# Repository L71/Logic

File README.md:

Logic signal processing Eurorack modules
========================================

* 4520 - 8bit binary counter/clock divider. Can trigger on both clock signal edges (determined by which input is used). 

* 234 - Sync clock divider, one pulse out for every 2,3 or 4 in. 

* Trigger - small module with 2x gate rising edge detectors, 2x inverters with button. Additional ORed output for the two edge detector outputs.

Panels and PCBs licensed cc-by-sa.

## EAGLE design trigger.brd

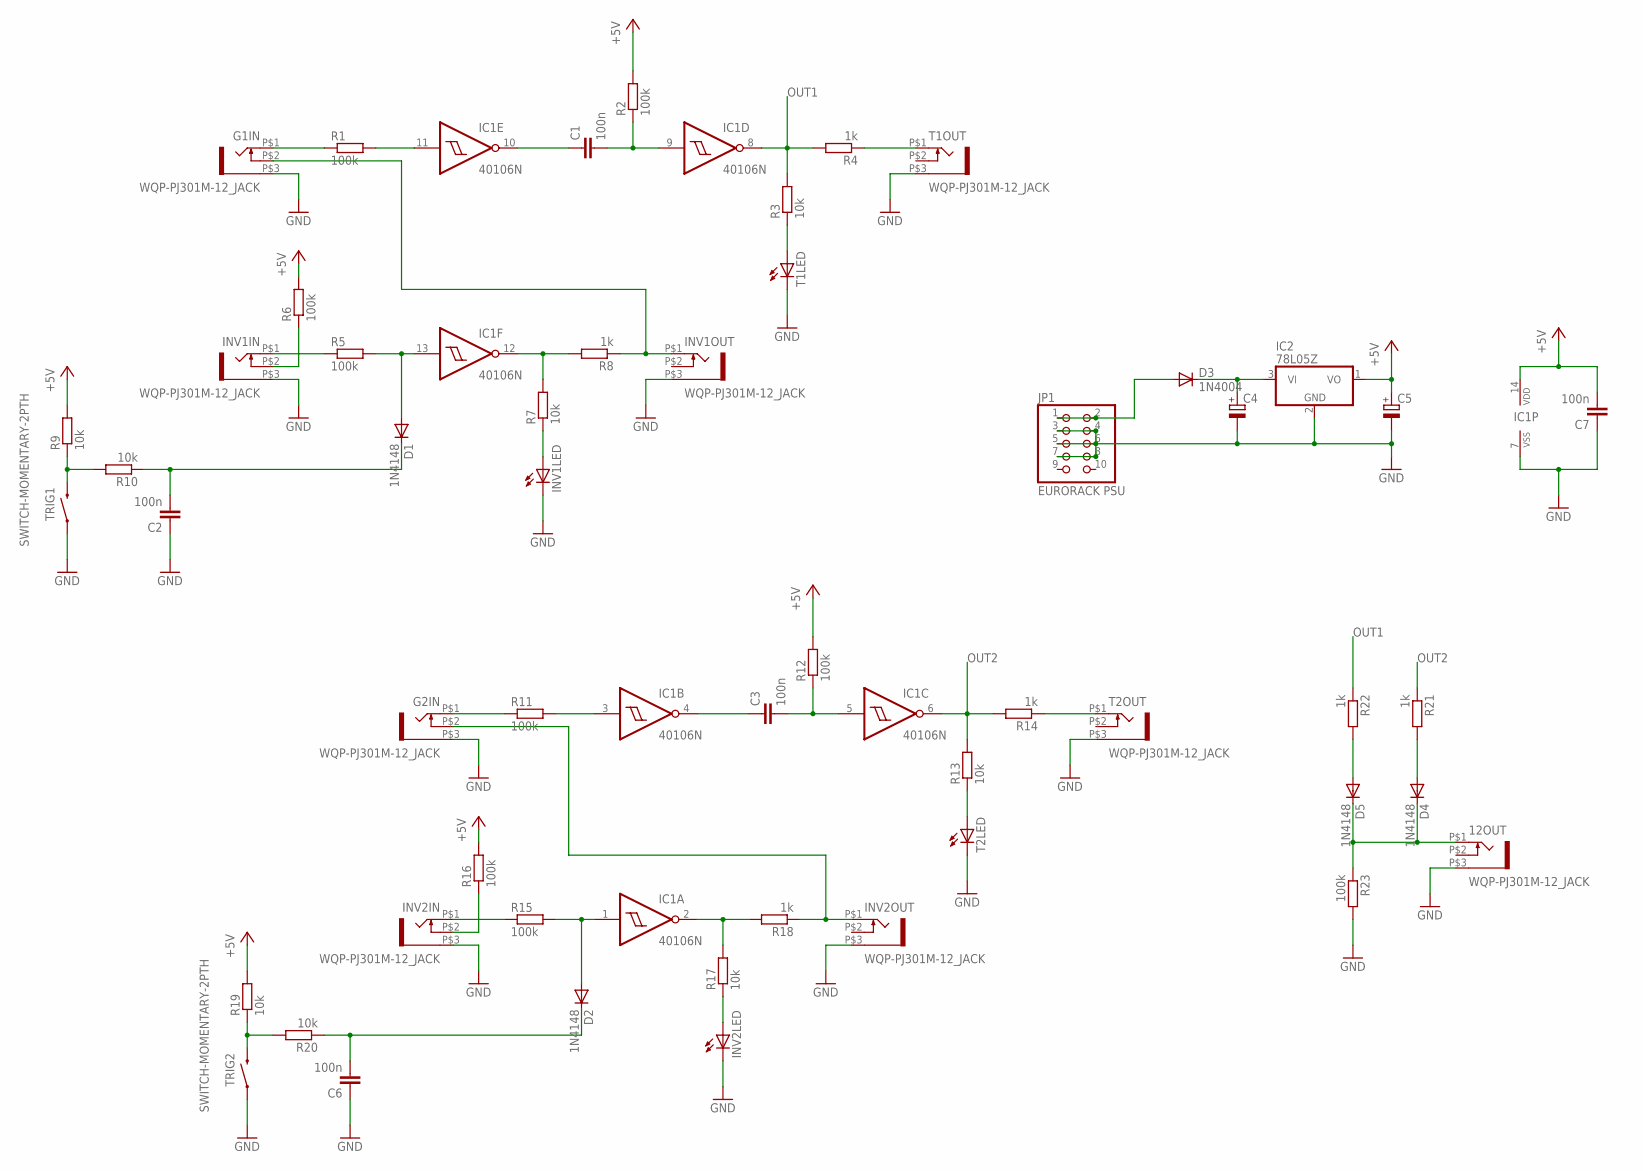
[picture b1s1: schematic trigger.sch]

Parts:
12OUT: WQP-PJ301M-12_JACK
C1, C2, C3, C6, C7: 100n; C025-025X050
C4, C5: CPOL-EUE2.5-5; E2,5-5
D1, D2, D4, D5: 1N4148; D-2.5
D3: 1N4004; D-2.5
G1IN, G2IN: WQP-PJ301M-12_JACK
IC1: 40106N; DIL14
IC2: 78L05Z; TO92
INV1IN, INV1OUT, INV2IN, INV2OUT: WQP-PJ301M-12_JACK
INV1LED, INV2LED: LED3MM
JP1: EURORACK PSU; 2X05
R1, R2, R5, R6, R11, R12, R15, R16, R23: 100k; 0204V
R3, R7, R9, R10, R13, R17, R19, R20: 10k; 0204V
R4, R8, R14, R18, R21, R22: 1k; 0204V
T1LED, T2LED: LED3MM
T1OUT, T2OUT: WQP-PJ301M-12_JACK
TRIG1, TRIG2: SWITCH-MOMENTARY-2PTH; TACTILE-PTH

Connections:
+5V: C5.+, C7.2, IC1.14 (VDD), IC2.1 (VO), R2.2, R6.2, R9.2, R12.2, R16.2, R19.2
+12V_IN: D3.A, JP1.1, JP1.2
GND: 12OUT.P$3 (1), C2.1, C4.-, C5.-, C6.1, C7.1, G1IN.P$3 (1), G2IN.P$3 (1), IC1.7 (VSS), IC2.2 (GND), INV1IN.P$3 (1), INV1LED.K (C), INV1OUT.P$3 (1), INV2IN.P$3 (1), INV2LED.K (C), INV2OUT.P$3 (1), JP1.3, JP1.4, JP1.5, JP1.6, JP1.7, JP1.8, R23.2, T1LED.K (C), T1OUT.P$3 (1), T2LED.K (C), T2OUT.P$3 (1), TRIG1.1, TRIG2.1
IN_1: G1IN.P$1 (2), R1.1
unnamed: 12OUT.P$1 (2), D4.C, D5.C, R23.1
unnamed: IC1.11 (I), R1.2
unnamed: C1.1, IC1.10 (O)
unnamed: C1.2, IC1.9 (I), R2.1
unnamed: D5.A, R22.2
unnamed: R3.1, T1LED.A
unnamed: R4.1, T1OUT.P$1 (2)
unnamed: IC1.12 (O), R7.2, R8.2
unnamed: INV1LED.A, R7.1
unnamed: G1IN.P$2 (3), INV1OUT.P$1 (2), R8.1
unnamed: INV1IN.P$1 (2), R5.1
unnamed: D1.A, IC1.13 (I), R5.2
unnamed: INV1IN.P$2 (3), R6.1
unnamed: C4.+, D3.C, IC2.3 (VI)
unnamed: R9.1, R10.2, TRIG1.3 (2)
unnamed: C2.2, D1.C, R10.1
unnamed: G2IN.P$1 (2), R11.1
unnamed: IC1.3 (I), R11.2
unnamed: C3.1, IC1.4 (O)
unnamed: C3.2, IC1.5 (I), R12.1
unnamed: D4.A, R21.2
unnamed: R13.1, T2LED.A
unnamed: R14.1, T2OUT.P$1 (2)
unnamed: IC1.2 (O), R17.2, R18.2
unnamed: INV2LED.A, R17.1
unnamed: G2IN.P$2 (3), INV2OUT.P$1 (2), R18.1
unnamed: INV2IN.P$1 (2), R15.1
unnamed: D2.A, IC1.1 (I), R15.2
unnamed: INV2IN.P$2 (3), R16.1
unnamed: R19.1, R20.2, TRIG2.3 (2)
unnamed: C6.2, D2.C, R20.1
OUT1: IC1.8 (O), R3.2, R4.2, R22.1
OUT2: IC1.6 (O), R13.2, R14.2, R21.1

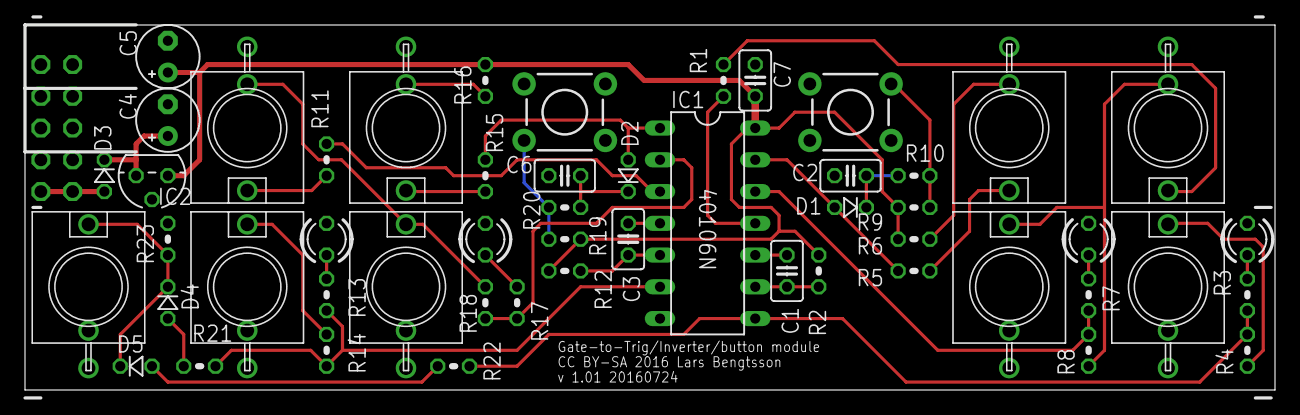
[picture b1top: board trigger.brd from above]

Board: 2 copper layers, 100.0 x 29.2 mm, 53 parts (1 on the bottom side), 37 nets.

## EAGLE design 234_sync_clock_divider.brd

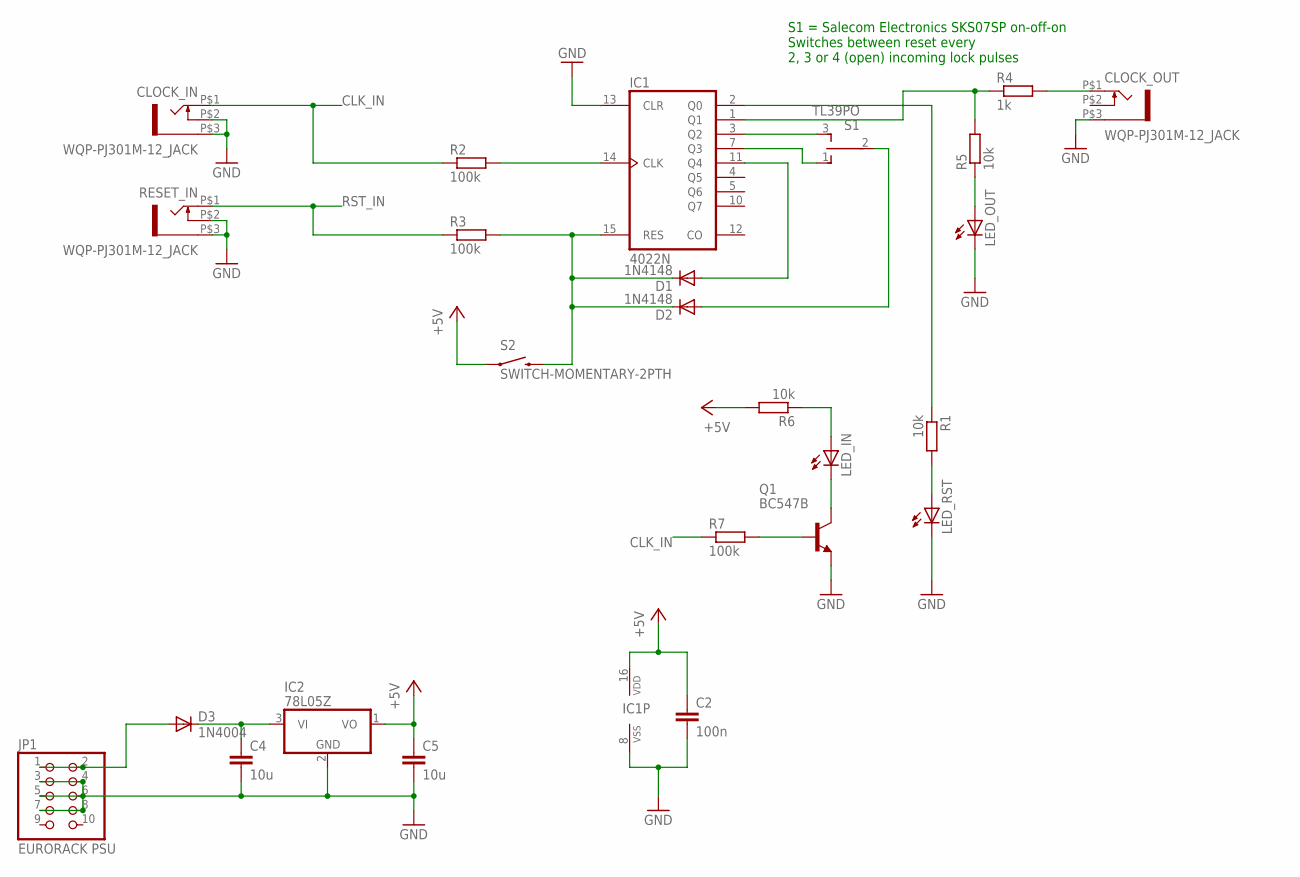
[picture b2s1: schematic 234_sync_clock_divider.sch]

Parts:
C2: 100n; C025-025X050
C4, C5: 10u; C1206K
CLOCK_IN: WQP-PJ301M-12_JACK
CLOCK_OUT: WQP-PJ301M-12_JACK
D1, D2: 1N4148; D-2.5
D3: 1N4004; D-2.5
IC1: 4022N; DIL16
IC2: 78L05Z; TO92
JP1: EURORACK PSU; 2X05
LED_IN: LED3MM
LED_OUT: LED3MM
LED_RST: LED3MM
Q1: BC547B; TO92
R1, R5, R6: 10k; 0204V
R2, R3, R7: 100k; 0204V
R4: 1k; 0204V
RESET_IN: WQP-PJ301M-12_JACK
S1: TL39PO; TL3XPO
S2: SWITCH-MOMENTARY-2PTH; TACTILE-PTH

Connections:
+5V: C2.1, C5.1, IC1.16 (VDD), IC2.1 (VO), R6.2, S2.1
+12V_IN: D3.A, JP1.1, JP1.2
CLK_IN: CLOCK_IN.P$1 (2), R2.1, R7.1
GND: C2.2, C4.2, C5.2, CLOCK_IN.P$2 (3), CLOCK_IN.P$3 (1), CLOCK_OUT.P$3 (1), IC1.8 (VSS), IC1.13 (CLR), IC2.2 (GND), JP1.3, JP1.4, JP1.5, JP1.6, JP1.7, JP1.8, LED_OUT.K (C), LED_RST.K (C), Q1.1 (E), RESET_IN.P$2 (3), RESET_IN.P$3 (1)
unnamed: LED_RST.A, R1.2
unnamed: IC1.14 (CLK), R2.2
unnamed: D1.C, D2.C, IC1.15 (RES), R3.2, S2.3 (2)
unnamed: IC1.2 (Q0), R1.1
unnamed: IC1.1 (Q1), R4.1, R5.2
unnamed: CLOCK_OUT.P$1 (2), R4.2
unnamed: LED_OUT.A, R5.1
unnamed: D1.A, IC1.11 (Q4)
unnamed: IC1.3 (Q2), S1.3 (S)
unnamed: IC1.7 (Q3), S1.1 (O)
unnamed: D2.A, S1.2
unnamed: C4.1, D3.C, IC2.3 (VI)
unnamed: LED_IN.A, R6.1
unnamed: LED_IN.K (C), Q1.3 (C)
unnamed: Q1.2 (B), R7.2
RST_IN: R3.1, RESET_IN.P$1 (2)

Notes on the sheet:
S1 = Salecom Electronics SKS07SP on-off-on Switches between reset every 2, 3 or 4 (open) incoming lock pulses

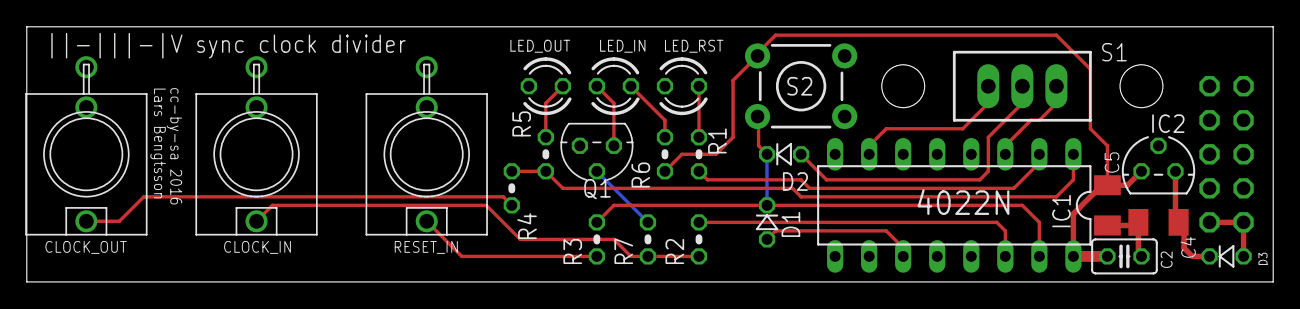
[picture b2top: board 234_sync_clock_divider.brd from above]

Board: 2 copper layers, 93.0 x 19.0 mm, 25 parts (1 on the bottom side), 20 nets.

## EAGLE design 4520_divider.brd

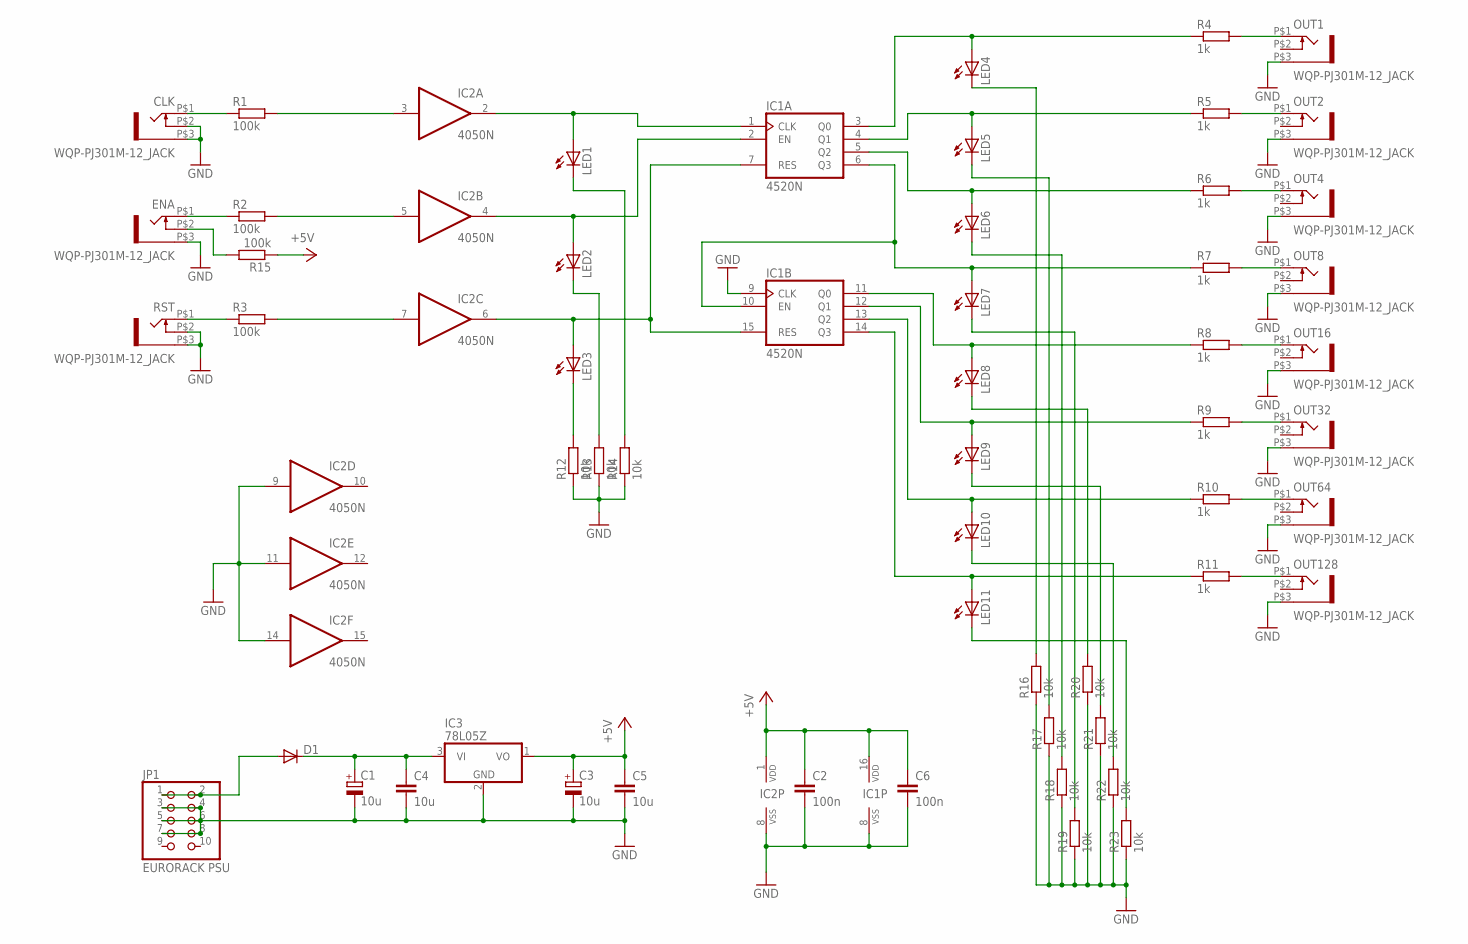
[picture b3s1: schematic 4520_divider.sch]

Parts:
C1, C3: 10u; E2,5-5
C2, C6: 100n; C025-025X050
C4, C5: 10u; C1206K
CLK: WQP-PJ301M-12_JACK
D1: DIODE-D-2.5; D-2.5
ENA: WQP-PJ301M-12_JACK
IC1: 4520N; DIL16
IC2: 4050N; DIL16
IC3: 78L05Z; TO92
JP1: EURORACK PSU; 2X05
LED1, LED2, LED3, LED4, LED5, LED6, LED7, LED8, LED9, LED10, LED11: LED3MM
OUT1, OUT2, OUT4, OUT8, OUT16, OUT32, OUT64, OUT128: WQP-PJ301M-12_JACK
R1, R2, R3, R15: 100k; 0204V
R4, R5, R6, R7, R8, R9, R10, R11: 1k; R1206
R12, R13, R14, R16, R17, R18, R19, R20, R21, R22, R23: 10k; R1206
RST: WQP-PJ301M-12_JACK

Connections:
+5V: C2.1, C3.+, C5.1, C6.1, IC1.16 (VDD), IC2.1 (VDD), IC3.1 (VO), R15.1
+12V_IN: D1.A, JP1.1, JP1.2
GND: C1.-, C2.2, C3.-, C4.2, C5.2, C6.2, CLK.P$2 (3), CLK.P$3 (1), ENA.P$3 (1), IC1.8 (VSS), IC1.9 (CLK), IC2.8 (VSS), IC2.9 (I), IC2.11 (I), IC2.14 (I), IC3.2 (GND), JP1.3, JP1.4, JP1.5, JP1.6, JP1.7, JP1.8, OUT1.P$3 (1), OUT2.P$3 (1), OUT4.P$3 (1), OUT8.P$3 (1), OUT16.P$3 (1), OUT32.P$3 (1), OUT64.P$3 (1), OUT128.P$3 (1), R12.1, R13.1, R14.1, R16.1, R17.1, R18.1, R19.1, R20.1, R21.1, R22.1, R23.1, RST.P$2 (3), RST.P$3 (1)
unnamed: OUT1.P$1 (2), R4.2
unnamed: IC1.4 (Q1), LED5.A, R5.1
unnamed: IC1.3 (Q0), LED4.A, R4.1
unnamed: LED4.K (C), R16.2
unnamed: OUT2.P$1 (2), R5.2
unnamed: OUT4.P$1 (2), R6.2
unnamed: C1.+, C4.1, D1.C, IC3.3 (VI)
unnamed: IC1.5 (Q2), LED6.A, R6.1
unnamed: LED5.K (C), R17.2
unnamed: LED6.K (C), R18.2
unnamed: LED7.K (C), R19.2
unnamed: LED8.K (C), R20.2
unnamed: LED9.K (C), R21.2
unnamed: LED10.K (C), R22.2
unnamed: LED11.K (C), R23.2
unnamed: OUT8.P$1 (2), R7.2
unnamed: OUT16.P$1 (2), R8.2
unnamed: OUT32.P$1 (2), R9.2
unnamed: OUT64.P$1 (2), R10.2
unnamed: OUT128.P$1 (2), R11.2
unnamed: IC1.6 (Q3), IC1.10 (EN), LED7.A, R7.1
unnamed: IC1.11 (Q0), LED8.A, R8.1
unnamed: IC1.12 (Q1), LED9.A, R9.1
unnamed: IC1.13 (Q2), LED10.A, R10.1
unnamed: IC1.14 (Q3), LED11.A, R11.1
unnamed: IC2.3 (I), R1.2
unnamed: IC2.5 (I), R2.2
unnamed: IC1.1 (CLK), IC2.2 (O), LED1.A
unnamed: IC1.2 (EN), IC2.4 (O), LED2.A
unnamed: IC1.7 (RES), IC1.15 (RES), IC2.6 (O), LED3.A
unnamed: LED3.K (C), R12.2
unnamed: LED2.K (C), R13.2
unnamed: LED1.K (C), R14.2
unnamed: IC2.7 (I), R3.2
unnamed: CLK.P$1 (2), R1.1
unnamed: ENA.P$1 (2), R2.1
unnamed: R3.1, RST.P$1 (2)
unnamed: ENA.P$2 (3), R15.2

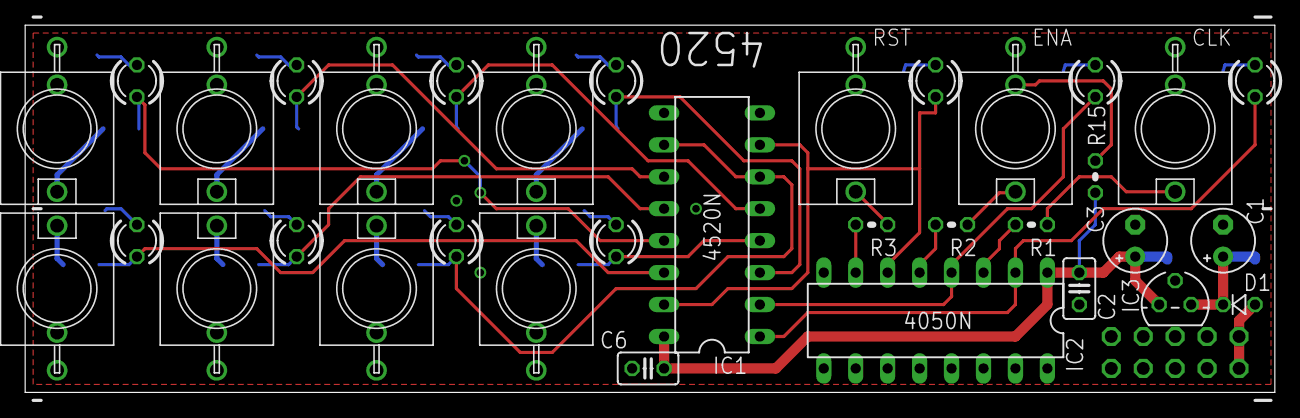
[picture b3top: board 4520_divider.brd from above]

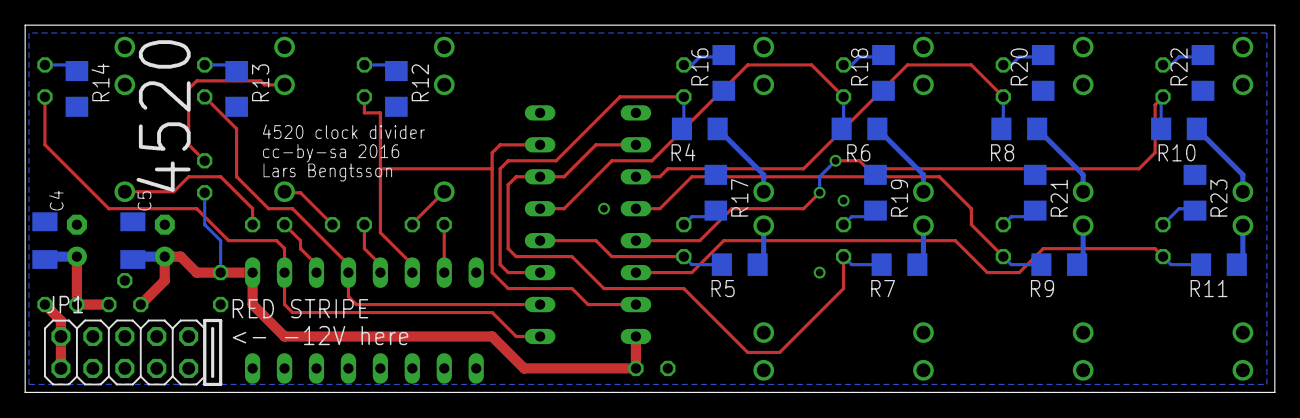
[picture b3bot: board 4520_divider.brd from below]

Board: 2 copper layers, 99.4 x 29.2 mm, 56 parts (22 on the bottom side), 41 nets.

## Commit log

2016-04-01 Initial add.
2016-04-01 Initial commit of works in progress.
2016-04-02 Moved a few resistors for clarity.
2016-04-02 Moved labels, added top layer ground plane, added alternative 1206 caps in PSU curcuit for use when low-profile electrolytic caps are hard to find.
2016-04-02 Panel done! =)
2016-04-02 Trimmed borders a bit.
2016-04-06 Initial add of 234 sync clock divider PCB + panel.
2016-04-06 Added repo info.
2016-04-11 Push button hole diameter increased to 3.5mm.
2016-05-23 Moved power connector - it was a bit too close to board edge. Added notice about CC license.
2016-07-18 Initial add. This is a module with two trigger buttons/inverters/trigger edge detectors.
2016-07-24 Minor routing improvement near common output. Added version/date stamp.
2016-07-27 Updated w/ trigger module info.

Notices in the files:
234_sync_clock_divider.brd:
cc-by-sa 2016
trigger.brd:
CC BY-SA 2016 Lars Bengtsson
parts and their libraries:
SparkFun-Electromechanical: Licensing: Creative Commons ShareAlike 4.0 International - https://creativecommons.org/licenses/by-sa/4.0
